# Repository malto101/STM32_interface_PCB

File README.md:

# STM32F103C8Tx PCB Design 

## Overview

This readme provides an overview of the design considerations and technical details for the STM32F103C8Tx-based PCB. The PCB includes a boot switch, exposed UART and I2C pins, utilizes SWD debugging for code uploading, and is powered via USB.

## PCB Features

- **Microcontroller:** STM32F103C8Tx
- **Boot Switch:** Allows for boot mode selection
- **UART and I2C Pins:** Exposed for external communication
- **Debugging:** Utilizes SWD (Serial Wire Debug) for code uploading and debugging
- **Power:** USB powered

## Filter Capacitor Calculation

For maintaining oscillator stability, a filter capacitor (CL) is required. I've calculated the value using the formula:

CL = 2 * (CL0 - CS) = 2 * (10 - 5) pF = 10 pF

This capacitor value helps ensure reliable oscillator performance, contributing to the overall stability of your design.

## Repository Structure

- `schematic/`: The schematic diagram of your PCB design.
- `DataSheet/`: Directory showcasing component presenting the PCB.
- `tutstm32.kicad_sch`: File containing the Schematic for the PCB.
- `tutstm32.kicad_pcb`: File containing the routing of the PCB.

## Getting Started

1. Clone or download this repository to your local machine.
2. Review the schematic and PCB layout diagrams for a visual design representation.

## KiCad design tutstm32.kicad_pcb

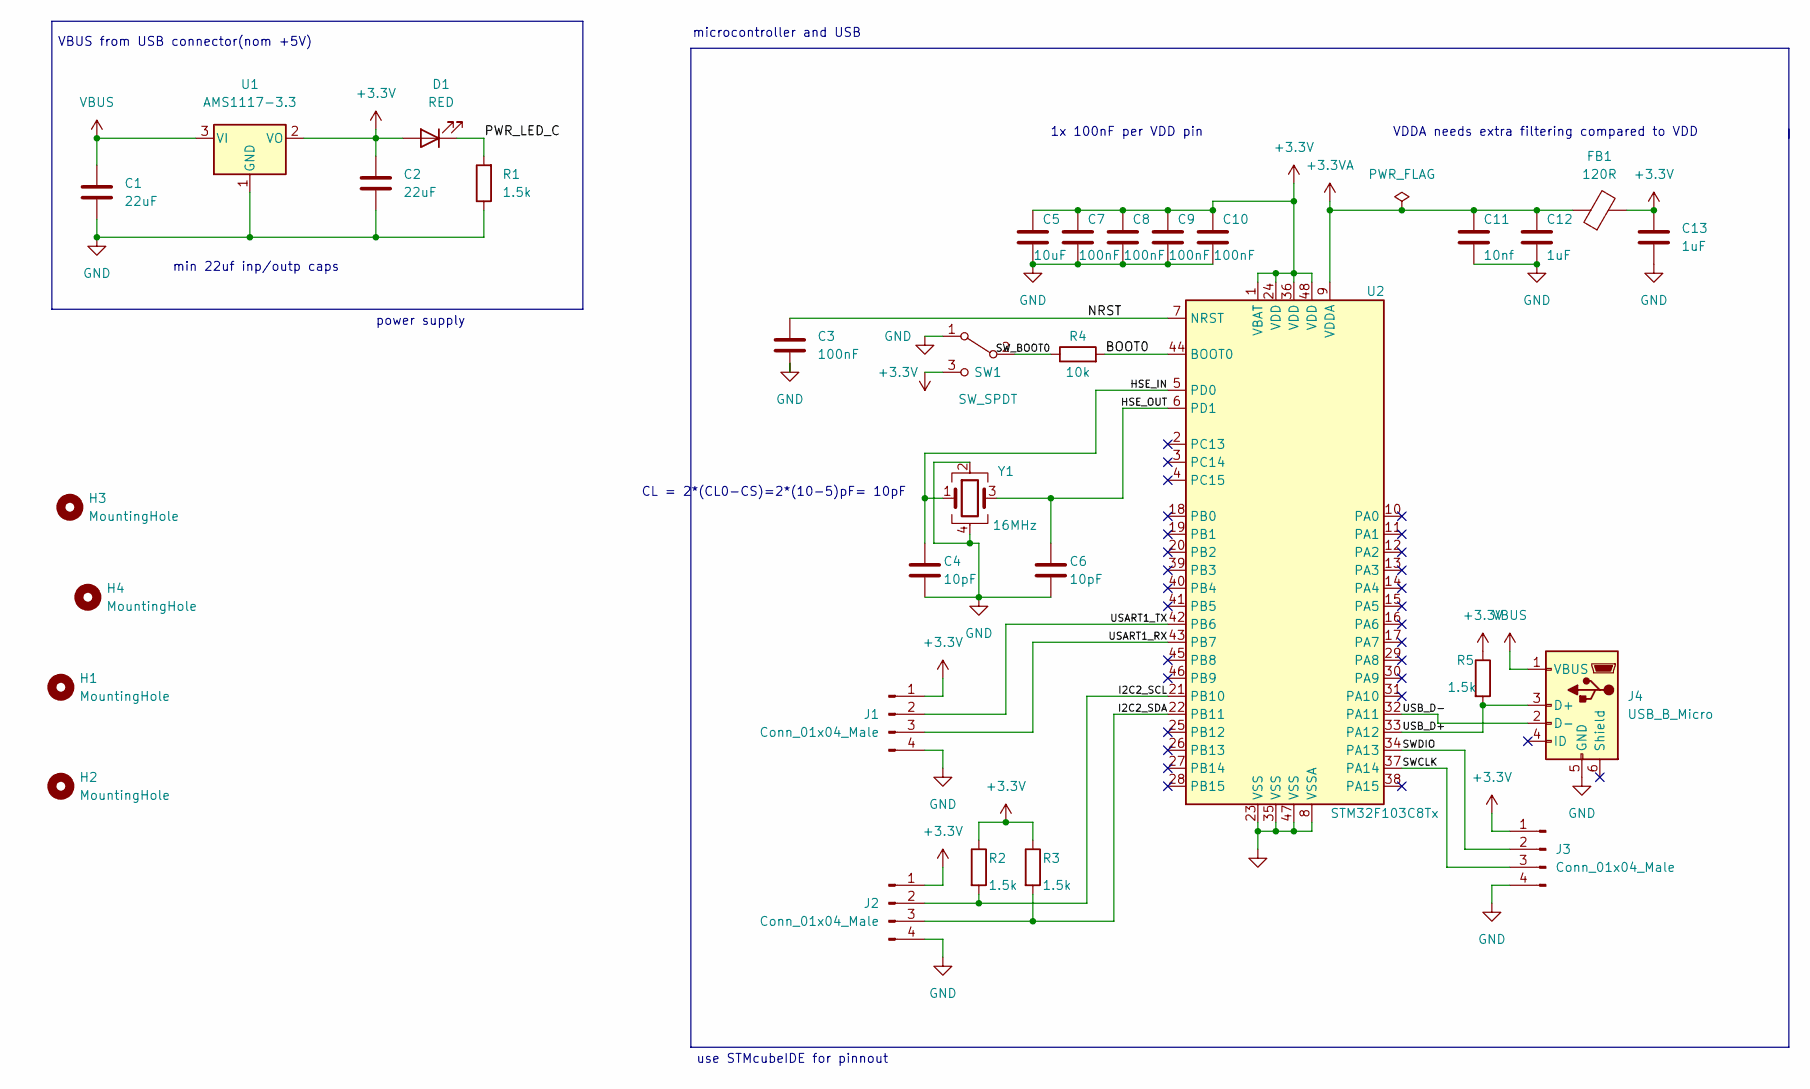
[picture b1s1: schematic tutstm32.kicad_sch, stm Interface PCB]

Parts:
C1, C2: 22uF; C_0805_2012Metric
C3, C7, C8, C9, C10: 100nF; C_0402_1005Metric
C4, C6: 10pF; C_0402_1005Metric
C5: 10uF; C_0603_1608Metric
C11: 10nf; C_0402_1005Metric
C12, C13: 1uF; C_0402_1005Metric
D1: RED; LED_0603_1608Metric
FB1: 120R; L_0603_1608Metric
H1, H2, H3, H4: MountingHole; MountingHole_2.1mm
J1, J2, J3: Conn_01x04_Male; PinHeader_1x04_P2.54mm_Vertical
J4: USB_B_Micro; USB_Micro-B_Wuerth_629105150521
R1, R2, R3, R5: 1.5k; R_0402_1005Metric
R4: 10k; R_0402_1005Metric
SW1: SW_SPDT; SW_SPDT_PCM12
U1: AMS1117-3.3; SOT-223-3_TabPin2
U2: STM32F103C8Tx; LQFP-48_7x7mm_P0.5mm
Y1: 16MHz; Crystal_SMD_3225-4Pin_3.2x2.5mm

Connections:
+3.3V: C2.1, C5.1, C7.1, C8.1, C9.1, C10.1, C13.1, D1.2 (A), FB1.2, J1.1, J2.1, J3.1, R2.1, R3.1, R5.1, SW1.3 (C), U1.2 (VO), U2.1 (VBAT), U2.24 (VDD), U2.36 (VDD), U2.48 (VDD)
+3.3VA: C11.1, C12.1, FB1.1, U2.9 (VDDA)
/BOOT0: R4.2, U2.44 (BOOT0)
/HSE_IN: C4.1, U2.5 (PD0), Y1.1
/HSE_OUT: C6.1, U2.6 (PD1), Y1.3
/I2C2_SCL: J2.2, R2.2, U2.21 (PB10)
/I2C2_SDA: J2.3, R3.2, U2.22 (PB11)
/NRST: C3.1, U2.7 (NRST)
/PWR_LED_C: D1.1 (K), R1.2
/SWCLK: J3.3, U2.37 (PA14)
/SWDIO: J3.2, U2.34 (PA13)
/SW_BOOT0: R4.1, SW1.2 (B)
/USART1_RX: J1.3, U2.43 (PB7)
/USART1_TX: J1.2, U2.42 (PB6)
/USB_D+: J4.3 (D+), R5.2, U2.33 (PA12)
/USB_D-: J4.2 (D-), U2.32 (PA11)
GND: C1.2, C2.2, C3.2, C4.2, C5.2, C6.2, C7.2, C8.2, C9.2, C10.2, C11.2, C12.2, C13.2, J1.4, J2.4, J3.4, J4.5 (GND), R1.1, SW1.1 (A), U1.1 (GND), U2.8 (VSSA), U2.23 (VSS), U2.35 (VSS), U2.47 (VSS), Y1.2, Y1.4
VBUS: C1.1, J4.1 (VBUS), U1.3 (VI)

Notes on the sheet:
CL = 2*(CL0-CS)=2*(10-5)pF= 10pF
VBUS from USB connector(nom +5V)
power supply
microcontroller and USB
1x 100nF per VDD pin
VDDA needs extra filtering compared to VDD
min 22uf inp/outp caps
use STMcubeIDE for pinnout

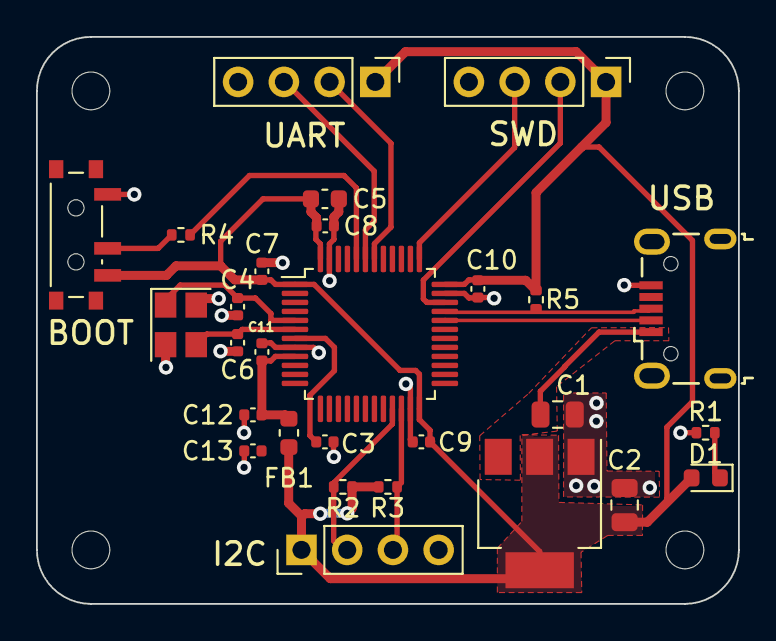
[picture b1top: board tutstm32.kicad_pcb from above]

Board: 2 copper layers, 39.0 x 31.5 mm, 32 parts (0 on the bottom side), 18 nets.
